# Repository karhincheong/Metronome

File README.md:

# Metronome

An electronic metronome powered by an ESP32-S3-WROOM Module, utilising a 160 x 128 LCD-TFT screen and a speaker

## Motivation

I find my phone too distracting when attending music class, hence I'm making this metronome on a separate device so that its simple and non-distracting

## BOM

### Components

| Item             | Description      | Quantity | Unit Price (USD) | Total Price (USD) | URL                                                | MOQ |
| ---------------- | ---------------- | -------- | ---------------- | ----------------- | -------------------------------------------------- | --- |
| Capacitors       | 0805 22 uF       | 1        | 0.0696           | 0.7               | https://www.lcsc.com/product-detail/C5674.html     | 10  |
|                  | 0805 4.7 uF      | 2        | 0.0267           | 0.53              | https://www.lcsc.com/product-detail/C1779.html     | 20  |
|                  | 0805 10 uF       | 1        | 0.0421           | 0.84              | https://www.lcsc.com/product-detail/C17024.html    | 20  |
|                  | 0805 0.1 uF      | 2        | 0.0061           | 0.15              | https://www.lcsc.com/product-detail/C476766.html   | 25  |
| LEDs             | 0805 YELLOW      | 1        | 0.0118           | 0.59              | https://www.lcsc.com/product-detail/C20608785.html | 50  |
|                  | 0805 BLUE        | 1        | 0.0078           | 0.78              | https://www.lcsc.com/product-detail/C19171391.html | 100 |
|                  | 0805 GREEN       | 1        | 0.0222           | 0.67              | https://www.lcsc.com/product-detail/C84260.html    | 30  |
|                  | 0805 RED         | 1        | 0.007            | 0.7               | https://www.lcsc.com/product-detail/C965812.html   | 100 |
| JST Connector    |                  | 1        | 0.0393           | 0.79              | https://www.lcsc.com/product-detail/C173752.html   | 20  |
| USB-C Receptacle |                  | 1        | 0.0877           | 0.44              | https://www.lcsc.com/product-detail/C2988369.html  | 5   |
| TFT-LCD          | ST7735 160\*128  | 1        | 3.2069           | 3.21              | https://www.lcsc.com/product-detail/C5329585.html  | 1   |
| Speaker          |                  | 1        | 0.818            | 0.82              | https://www.lcsc.com/product-detail/C530531.html   | 1   |
| Resistors        | 0805 2k          | 2        | 0.0031           | 0.31              | https://www.lcsc.com/product-detail/C2907248.html  | 100 |
|                  | 0805 10k         | 4        | 0.0031           | 0.31              | https://www.lcsc.com/product-detail/C2930231.html  | 100 |
|                  | 0805 5.1k        | 2        | 0.0028           | 0.28              | https://www.lcsc.com/product-detail/C27834.html    | 100 |
|                  | 0805 330k        | 1        | 0.004            | 0.4               | https://www.lcsc.com/product-detail/C114528.html   | 100 |
|                  | 0805 15k         | 1        | 0.0033           | 0.33              | https://www.lcsc.com/product-detail/C2930170.html  | 100 |
|                  | 0805 470Ω        | 3        | 0.003            | 0.3               | https://www.lcsc.com/product-detail/C2907267.html  | 100 |
| Rotary Encoders  | EC11             | 3        | 1.9069           | 5.72              | https://www.lcsc.com/product-detail/C470742.html   | 1   |
| Slide Switch     | SPST             | 1        | 0.0541           | 0.54              | https://www.lcsc.com/product-detail/C7498220.html  | 10  |
| Push Buttons     | 4.5 x 4.5 mm     | 2        | 0.0109           | 0.55              | https://www.lcsc.com/product-detail/C52092029.html | 50  |
|                  | ⌀ 10 mm          | 1        | 0.3832           | 0.38              | https://www.lcsc.com/product-detail/C268254.html   | 1   |
| Thermistor       | NTC 10k          | 1        | 0.685            | 0.69              | https://www.lcsc.com/product-detail/C17376775.html | 1   |
| ESP32-S3-WROOM-1 |                  | 1        | 4.5417           | 4.54              | https://www.lcsc.com/product-detail/C2913197.html  | 1   |
| MCP73871         |                  | 1        | 4.5329           | 4.53              | https://www.lcsc.com/product-detail/C5121473.html  | 1   |
| AMS1117          | 3.3V Variant     | 1        | 0.0424           | 0.04              | https://www.lcsc.com/product-detail/C347222.html   | 1   |
| MAX98357A        |                  | 1        | 1.3362           | 1.34              | https://www.lcsc.com/product-detail/C910544.html   | 1   |
| USBLC6-2SC6      |                  | 1        | 0.164            | 0.82              | https://www.lcsc.com/product-detail/C7519.html     | 5   |
| Battery          | 3.7V LiPO 300mAh | 1        | 0.79             | 0.79              | https://item.szlcsc.com/mro/419942.html            | 1   |
|                  |                  |          |                  |                   |                                                    |     |
| TOTAL            |                  |          |                  | 32.09             |                                                    |     |

### Other Costs Incurred

| Item         | Description       | Price |
| ------------ | ----------------- | ----- |
| PCB Printing | JLCPCB            | 2.00  |
| Shipping     | UPS Express Saver | 9.24  |

## Assembly Instructions

| Folder        | Description                       |
| ------------- | --------------------------------- |
| `kicad/`      | KiCAD files                       |
| `3d/`         | 3D files for the case and the PCB |
| `src/`        | Source Code for firmware          |
| `production/` | Files for manufacturers           |

1. Solder the components by hand onto the PCB. You may opt for PCBA for some of the components but it's expensive.
2. Flash firmware in `src/main` onto the PCB by connecting your computer to the USB-C on the PCB. You may also have to press down on BOOT and RESET for it to enter serial download mode
3. 3D Print the case of the the PCB.
4. Install the PCB into the case by screwing the PCB down using 4 M2 screws onto the 4 holes.

## Schematic Diagram

For clearer version, please refer `schematics.pdf`, or maybe you're trying to attract bugs ...

## PCB Layout

## PCB Render

You may refer to `3d/pcb3d.step` but note that there will not be any silkscreen or solder mask on it

## Case

Refer to `3d/metronomecase.step` or `3d/metronomecase.f3d` if you use Autodesk Fusion

## Project Zine

Uncompressed version at `zine.pdf`

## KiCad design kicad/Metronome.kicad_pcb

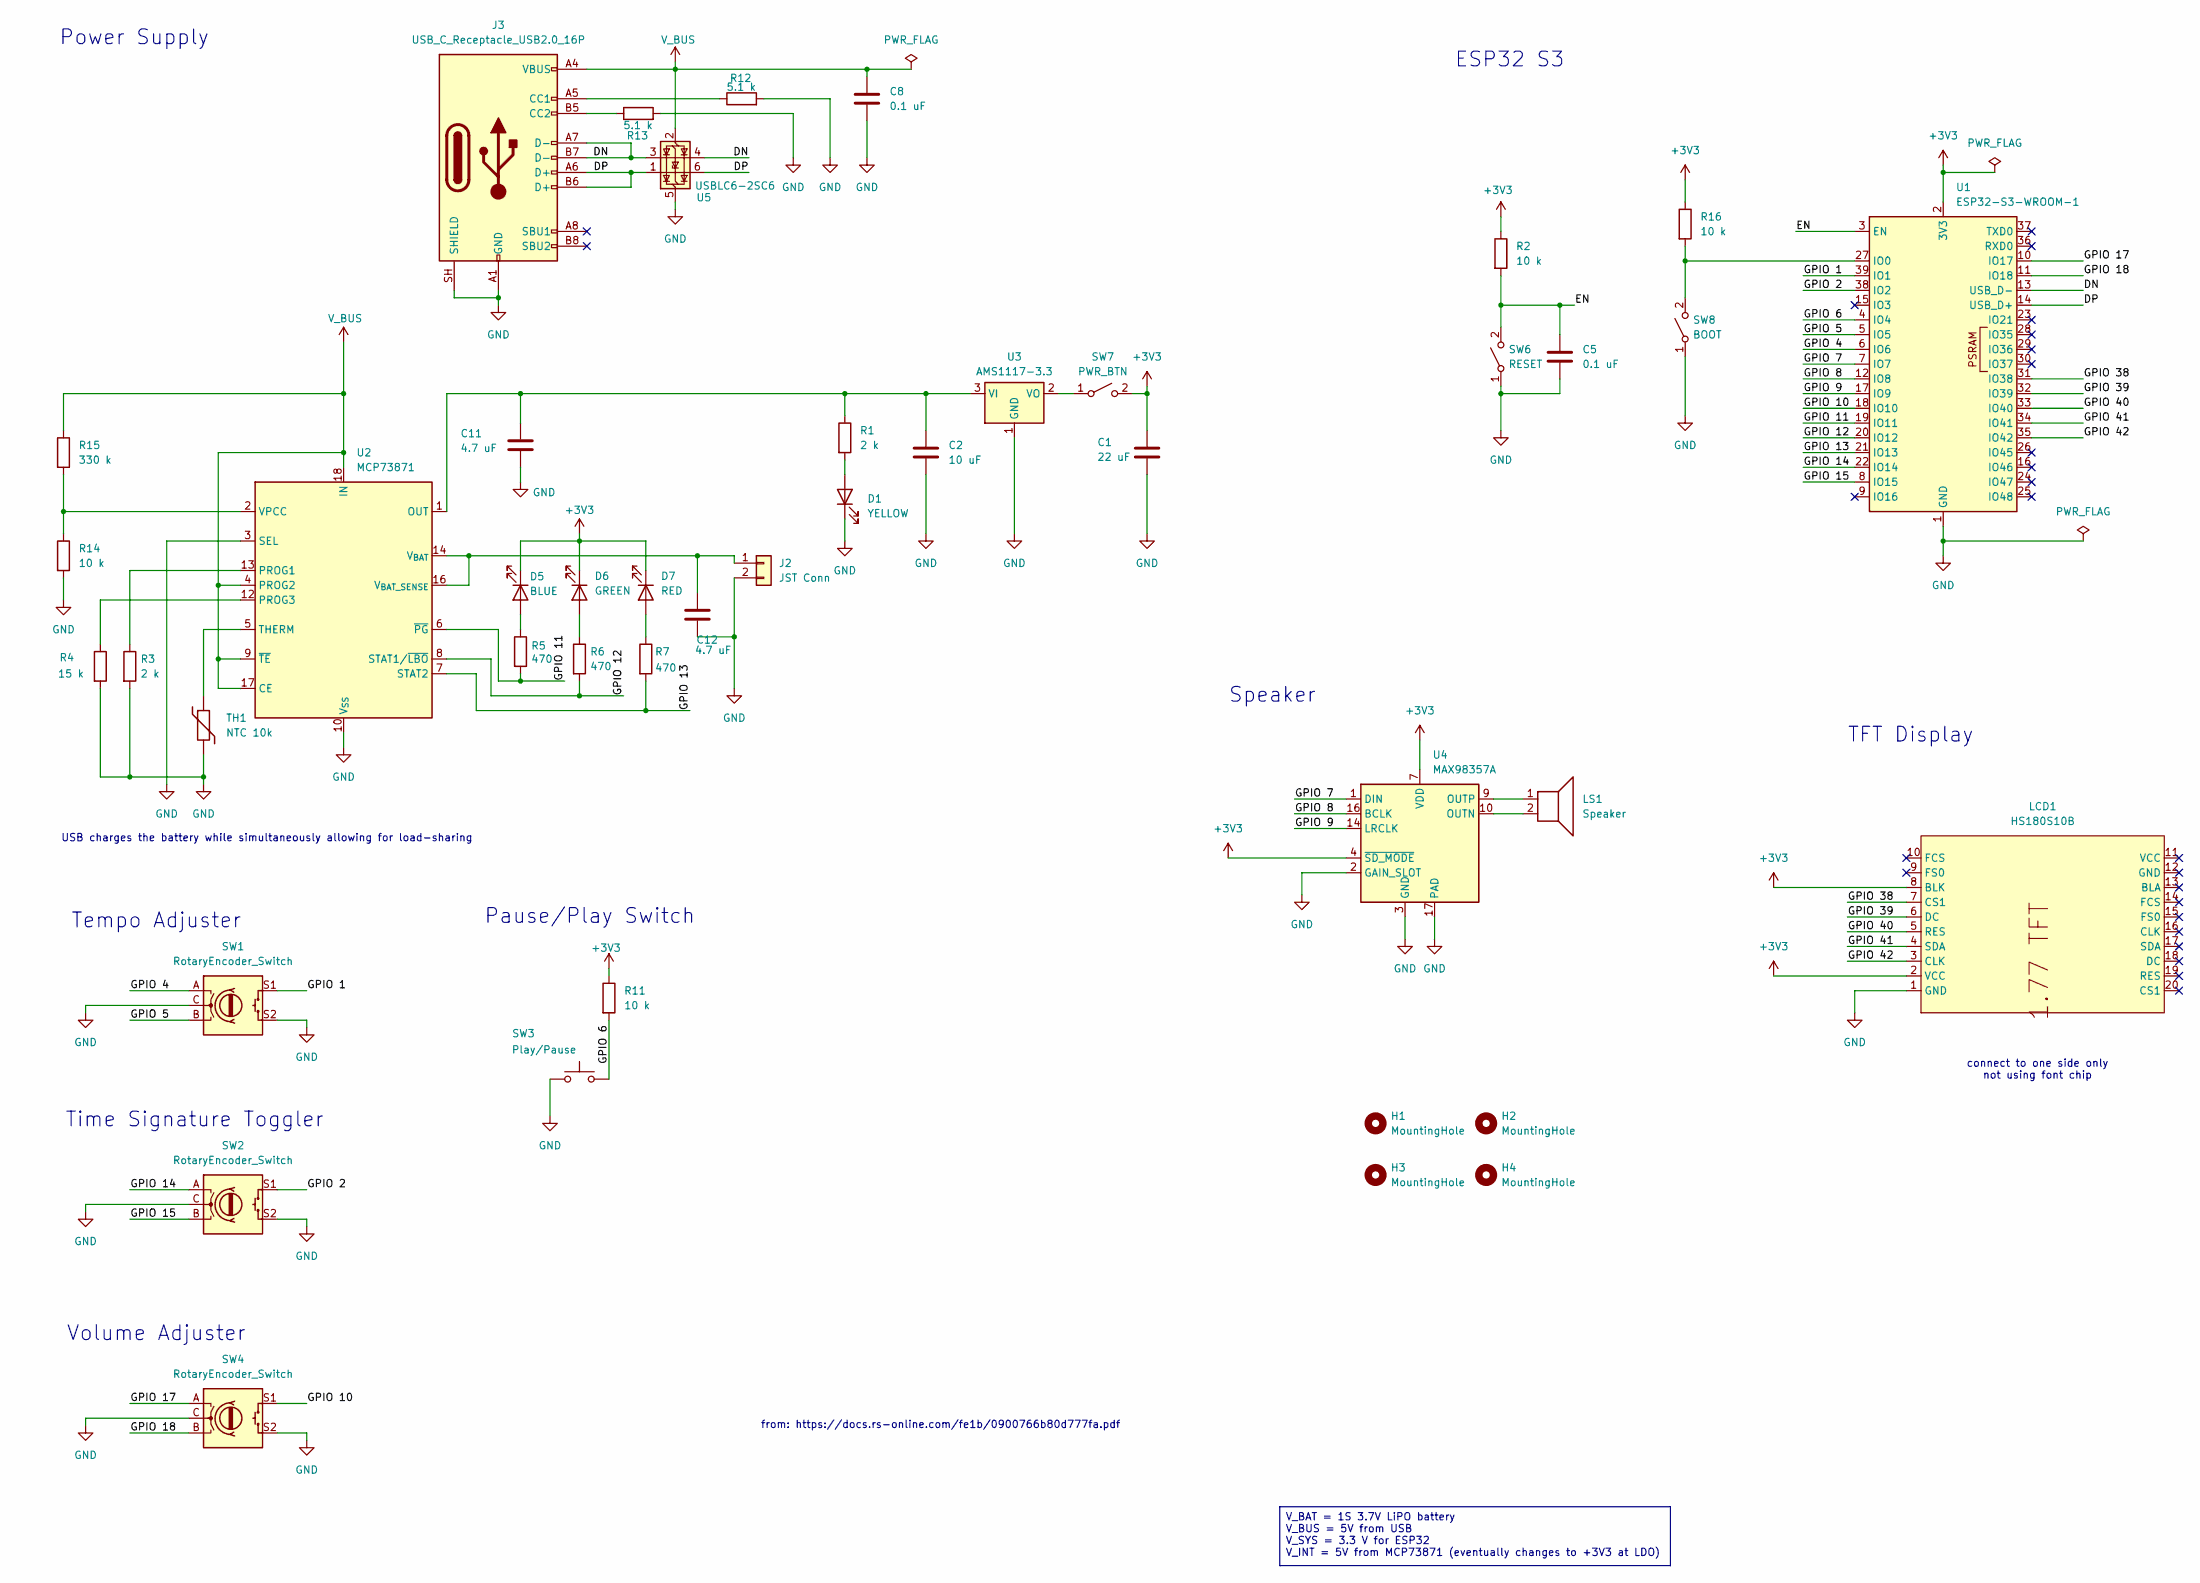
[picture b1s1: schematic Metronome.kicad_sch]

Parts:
C1: 22 uF; C_0805_2012Metric_Pad1.18x1.45mm_HandSolder
C2: 10 uF; C_0805_2012Metric_Pad1.18x1.45mm_HandSolder
C5, C8: 0.1 uF; C_0805_2012Metric_Pad1.18x1.45mm_HandSolder
C11, C12: 4.7 uF; C_0805_2012Metric_Pad1.18x1.45mm_HandSolder
D1: YELLOW; LED_0805_2012Metric_Pad1.15x1.40mm_HandSolder
D5: BLUE; LED_0805_2012Metric_Pad1.15x1.40mm_HandSolder
D6: GREEN; LED_0805_2012Metric_Pad1.15x1.40mm_HandSolder
D7: RED; LED_0805_2012Metric_Pad1.15x1.40mm_HandSolder
H1, H2, H3, H4: MountingHole; MountingHole_2.2mm_M2_DIN965
J2: JST Conn; JST_EH_S2B-EH_1x02_P2.50mm_Horizontal
J3: USB_C_Receptacle_USB2.0_16P; USB_C_Receptacle_GCT_USB4105-xx-A_16P_TopMnt_Horizontal
LCD1: HS180S10B; LCD-TH_L56.0-W35.0-P2.54_HS180S10B; MPN HS180S10B; LCSC Part C5329585
LS1: Speaker; SPK-TH_BD23.0-P10.00-D0.8-L-RD
R1, R3: 2 k; R_0805_2012Metric_Pad1.20x1.40mm_HandSolder
R2, R11, R14, R16: 10 k; R_0805_2012Metric_Pad1.20x1.40mm_HandSolder
R4: 15 k; R_0805_2012Metric_Pad1.20x1.40mm_HandSolder
R5, R6, R7: 470; R_0805_2012Metric_Pad1.20x1.40mm_HandSolder
R12, R13: 5.1 k; R_0805_2012Metric_Pad1.20x1.40mm_HandSolder
R15: 330 k; R_0805_2012Metric_Pad1.20x1.40mm_HandSolder
SW1, SW2, SW4: RotaryEncoder_Switch; RotaryEncoder_Alps_EC11E-Switch_Vertical_H20mm
SW3: Play/Pause; CONN-TH_PB-05B-R
SW6: RESET; SW-SMD_4P-L4.5-W4.5-P3.00-LS7.0_TS-1009S-03826
SW7: PWR_BTN; SW_SPDT_Shouhan_MSK12C02
SW8: BOOT; SW-SMD_4P-L4.5-W4.5-P3.00-LS7.0_TS-1009S-03826
TH1: NTC 10k; R0805
U1: ESP32-S3-WROOM-1
U2: MCP73871; QFN-20-1EP_4x4mm_P0.5mm_EP2.5x2.5mm
U3: AMS1117-3.3; SOT-223-3_TabPin2
U4: MAX98357A; TQFN-16-1EP_3x3mm_P0.5mm_EP1.23x1.23mm
U5: USBLC6-2SC6; SOT-23-6

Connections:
+3V3: C1.1, D5.1 (K), D6.1 (K), D7.1 (K), LCD1.2 (VCC), LCD1.8 (BLK), R2.1, R11.1, R16.1, SW7.2 (B), U1.2 (3V3), U4.4 (~SD_MODE), U4.7 (VDD), U4.8 (VDD)
/DN: J3.A7 (D-), J3.B7 (D-), U1.13 (USB_D-), U5.3 (I/O2), U5.4 (I/O2)
/DP: J3.A6 (D+), J3.B6 (D+), U1.14 (USB_D+), U5.1 (I/O1), U5.6 (I/O1)
/EN: C5.1, R2.2, SW6.2 (B), U1.3 (EN)
/GPIO 1: SW1.S1, U1.39 (IO1)
/GPIO 2: SW2.S1, U1.38 (IO2)
/GPIO 4: SW1.A, U1.6 (IO6)
/GPIO 5: SW1.B, U1.5 (IO5)
/GPIO 6: R11.2, SW3.2, U1.4 (IO4)
/GPIO 7: U1.7 (IO7), U4.1 (DIN)
/GPIO 8: U1.12 (IO8), U4.16 (BCLK)
/GPIO 9: U1.17 (IO9), U4.14 (LRCLK)
/GPIO 10: SW4.S1, U1.18 (IO10)
/GPIO 11: R5.2, U1.19 (IO11), U2.6 (~PG)
/GPIO 12: R6.2, U1.20 (IO12), U2.8 (STAT1/~LBO)
/GPIO 13: R7.2, U1.21 (IO13), U2.7 (STAT2)
/GPIO 14: SW2.A, U1.22 (IO14)
/GPIO 15: SW2.B, U1.8 (IO15)
/GPIO 17: SW4.A, U1.10 (IO17)
/GPIO 18: SW4.B, U1.11 (IO18)
/GPIO 38: LCD1.7 (CS1), U1.31 (IO38)
/GPIO 39: LCD1.6 (DC), U1.32 (IO39)
/GPIO 40: LCD1.5 (RES), U1.33 (IO40)
/GPIO 41: LCD1.4 (SDA), U1.34 (IO41)
/GPIO 42: LCD1.3 (CLK), U1.35 (IO42)
GND: C1.2, C2.2, C5.2, C8.2, C11.2, C12.2, D1.1 (K), J2.2, J3.A1 (GND), J3.A12 (GND), J3.B1 (GND), J3.B12 (GND), J3.SH (SHIELD), LCD1.1 (GND), R3.2, R4.2, R12.2, R13.2, R14.2, SW1.C, SW1.S2, SW2.C, SW2.S2, SW3.1, SW4.C, SW4.S2, SW6.1 (A), SW8.1 (A), TH1.2, U1.1 (GND), U1.40 (GND), U1.41 (GND), U2.3 (SEL), U2.10 (V_{SS}), U2.11 (V_{SS}), U2.21 (V_{SS}), U3.1 (GND), U4.2 (GAIN_SLOT), U4.3 (GND), U4.11 (GND), U4.15 (GND), U4.17 (PAD), U5.5 (VBUS)
unnamed: D1.2 (A), R1.2
unnamed: D5.2 (A), R5.1
unnamed: D6.2 (A), R6.1
unnamed: D7.2 (A), R7.1
unnamed: C12.1, J2.1, U2.14 (V_{BAT}), U2.15 (V_{BAT}), U2.16 (V_{BAT_SENSE})
unnamed: J3.A5 (CC1), R12.1
unnamed: J3.B5 (CC2), R13.1
unnamed: SW7.1 (A), U3.2 (VO)
unnamed: R16.2, SW8.2 (B), U1.27 (IO0)
unnamed: R3.1, U2.13 (PROG1)
unnamed: R4.1, U2.12 (PROG3)
unnamed: TH1.1, U2.5 (THERM)
unnamed: R14.1, R15.2, U2.2 (VPCC)
unnamed: C2.1, C11.1, R1.1, U2.1 (OUT), U2.20 (OUT), U3.3 (VI)
unnamed: LS1.2, U4.10 (OUTN)
unnamed: LS1.1, U4.9 (OUTP)
V_BUS: C8.1, J3.A4 (VBUS), J3.A9 (VBUS), J3.B4 (VBUS), J3.B9 (VBUS), R15.1, U2.4 (PROG2), U2.9 (~TE), U2.17 (CE), U2.18 (IN), U2.19 (IN), U5.2 (GND)

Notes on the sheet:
Power Supply
ESP32 S3
TFT Display
USB charges the battery while simultaneously allowing for load-sharing
Tempo Adjuster
Speaker
Time Signature Toggler
connect to one side only not using font chip
Volume Adjuster
from: https://docs.rs-online.com/fe1b/0900766b80d777fa.pdf
Pause/Play Switch
V_BAT = 1S 3.7V LiPO battery V_BUS = 5V from USB V_SYS = 3.3 V for ESP32 V_INT = 5V from MCP73871 (eventually changes to +3V3 at LDO)

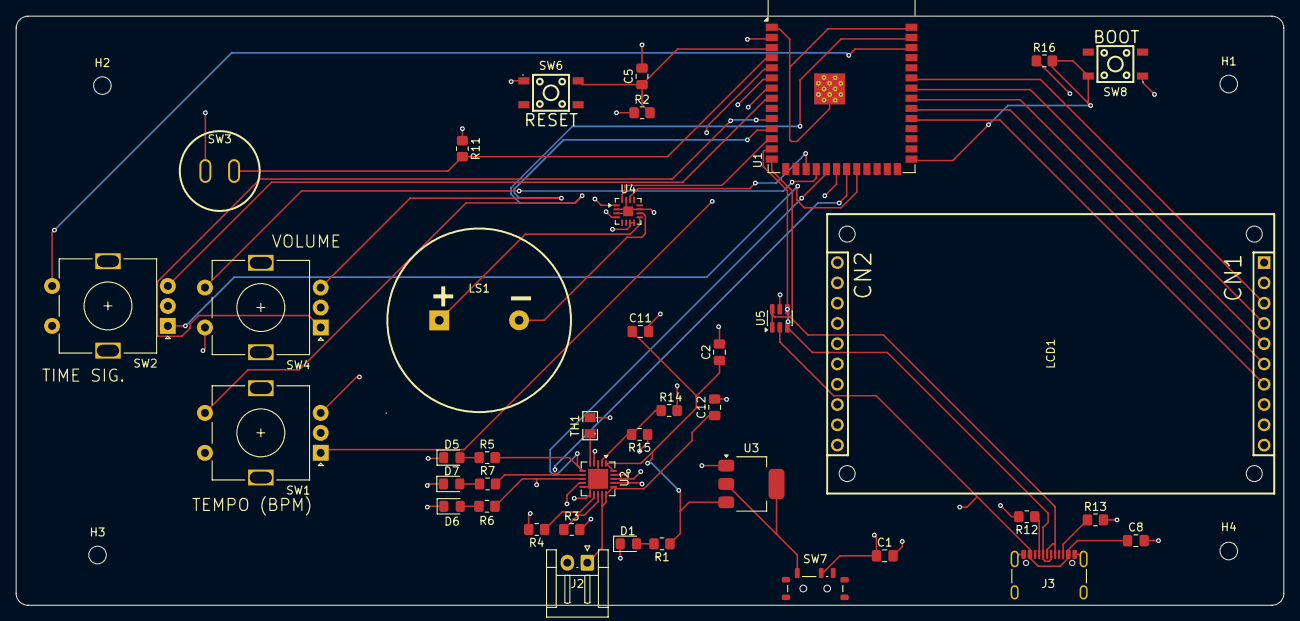
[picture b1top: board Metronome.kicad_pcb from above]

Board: 4 copper layers, 158.8 x 73.8 mm, 44 parts (0 on the bottom side), 43 nets.

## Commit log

2026-06-20 Uploading Files directly via Github
    cuz smh nothing shows up here after git push
2026-06-21 Updated Firmware
2026-06-21 Updated display firmware
2026-06-21 Updated main firmware
2026-06-21 Updated speaker firmware
2026-06-21 Renamed BOM_metronome.csv to BOM.csv
2026-06-21 added firmware instructions
